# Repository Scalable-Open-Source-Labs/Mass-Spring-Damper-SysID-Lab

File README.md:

# Mass Spring Damper SysID Lab

A low-cost dynamics lab that allows students to perform System Identification on a real Mass-Spring-Damper system.

This is the source repo where you can download files for manufacturing: hardware, firmware, and enclosure design files. If you're looking for usage instructions or lab notes, head to the [user guide](https://monasheng.gitbook.io/scalable-labs/mass-spring-damper-sysid).

*Designed by Michael Ruppe for Monash University in partnership with MathWorks®*

## Repo map

| Path | What it is |
|---|---|
| [`PCB/`](PCB/README.md) | KiCad hardware source for the main board and carriage |
| [`Enclosure/`](Enclosure/README.md) | 3D-printable case, guide rail, and lasercut acrylic lid |
| [`firmware-mass-spring-damper-sys-id-lab/`](firmware-mass-spring-damper-sys-id-lab/README.md) | Arduino sketch for the RP2040 main board |
| [`Images/`](Images/) | Photos used in the assembly guide |
| [`Assembly-Instructions.md`](Assembly-Instructions.md) | Step-by-step mechanical build guide |
| [`Programming-Instructions.md`](Programming-Instructions.md) | Flashing and firmware dev setup |
| [`Ordering-Instructions.md`](Ordering-Instructions.md) | Bill of materials and where to order/fabricate each part |
| [`JLCPCB-Ordering-Instructions.md`](JLCPCB-Ordering-Instructions.md) | Step-by-step JLCPCB order for the fabricated and assembled boards |
| [`RELEASING.md`](RELEASING.md) | Maintainer checklist for cutting a tagged release |

## Getting started

- [Ordering Instructions](Ordering-Instructions.md)
  - [JLCPCB Ordering Instructions](JLCPCB-Ordering-Instructions.md)
- [Assembly Instructions](Assembly-Instructions.md)
- [Programming Instructions](Programming-Instructions.md)
- [Latest Project Release](https://github.com/Scaleable-Open-Source-Labs/Mass-Spring-Damper-SysID-Lab/releases/latest) - A downloadable bundle of all project files to complete this project: 3D Printing, PCBA, Lasercutting

## License

This project is licensed under the [MIT License](LICENSE).

Bundled third-party content — KiCad symbol/footprint libraries and vendor 3D step models under `PCB/main-board/packages3D/` and `PCB/carriage/CAD/`, and the patched `LedControl` fork used by the firmware (see [firmware README](firmware-mass-spring-damper-sys-id-lab/README.md)) — retains its original license terms.

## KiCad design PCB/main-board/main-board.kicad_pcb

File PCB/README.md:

# PCB

## KiCad Projects

| Project | Purpose |
|---|---|
| [`main-board/`](main-board/) | RP2040 controller board. Reads the linear encoder, drives the 7-segment display, exposes captured motion data over USB as a virtual FAT12 drive |
| [`carriage/`](carriage/) | The moving carriage PCB that rides the guide rail, carrying the linear encoder strip |

## Datasheets

[`Datasheet/`](Datasheet/) Each schematic symbol's `Datasheet` field links to it with a path relative to its own project folder (e.g. `../Datasheet/SMTSO.pdf`), so this directory should only ever contain files that a `.kicad_sch` actually references. Call up a datasheet from within the schematic editor by hovering over a symbol and pressing the 'D' key.

Datasheets for parts that aren't placed as KiCad components (hand-assembly hardware sourced in [Ordering-Instructions.md](../Ordering-Instructions.md), like the carriage-capture bolt) belong in the root [`Datasheets/`](../Datasheets/) directory instead, not here.

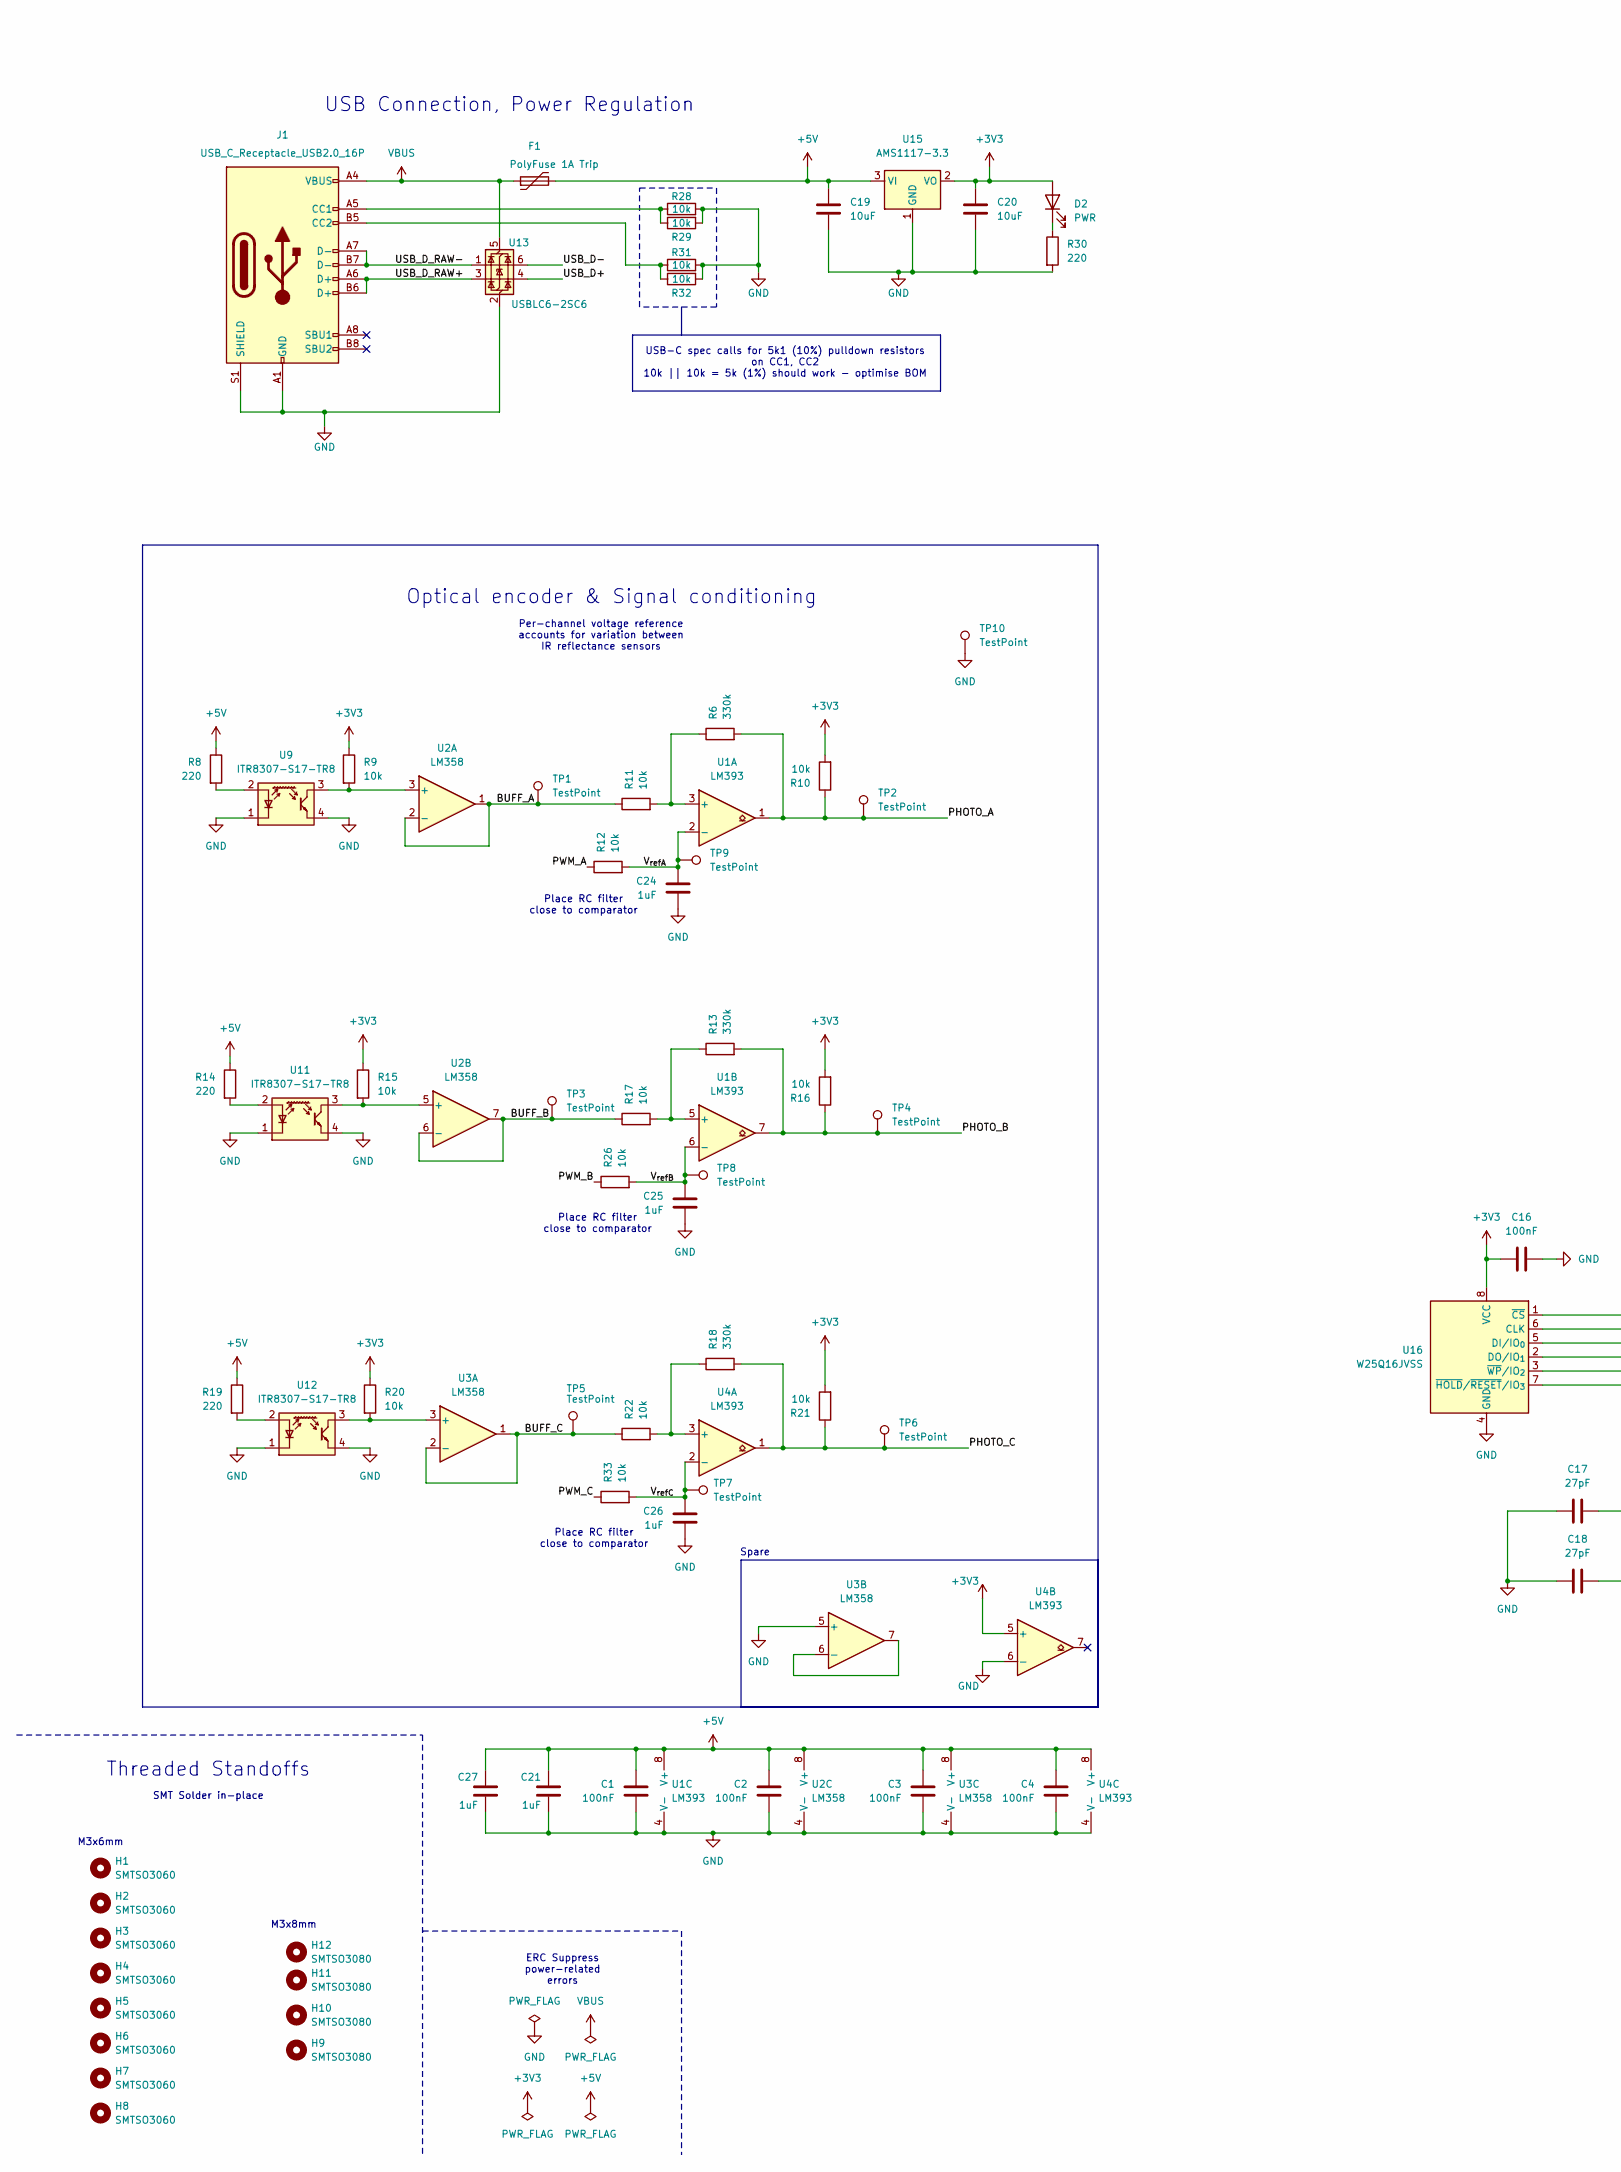
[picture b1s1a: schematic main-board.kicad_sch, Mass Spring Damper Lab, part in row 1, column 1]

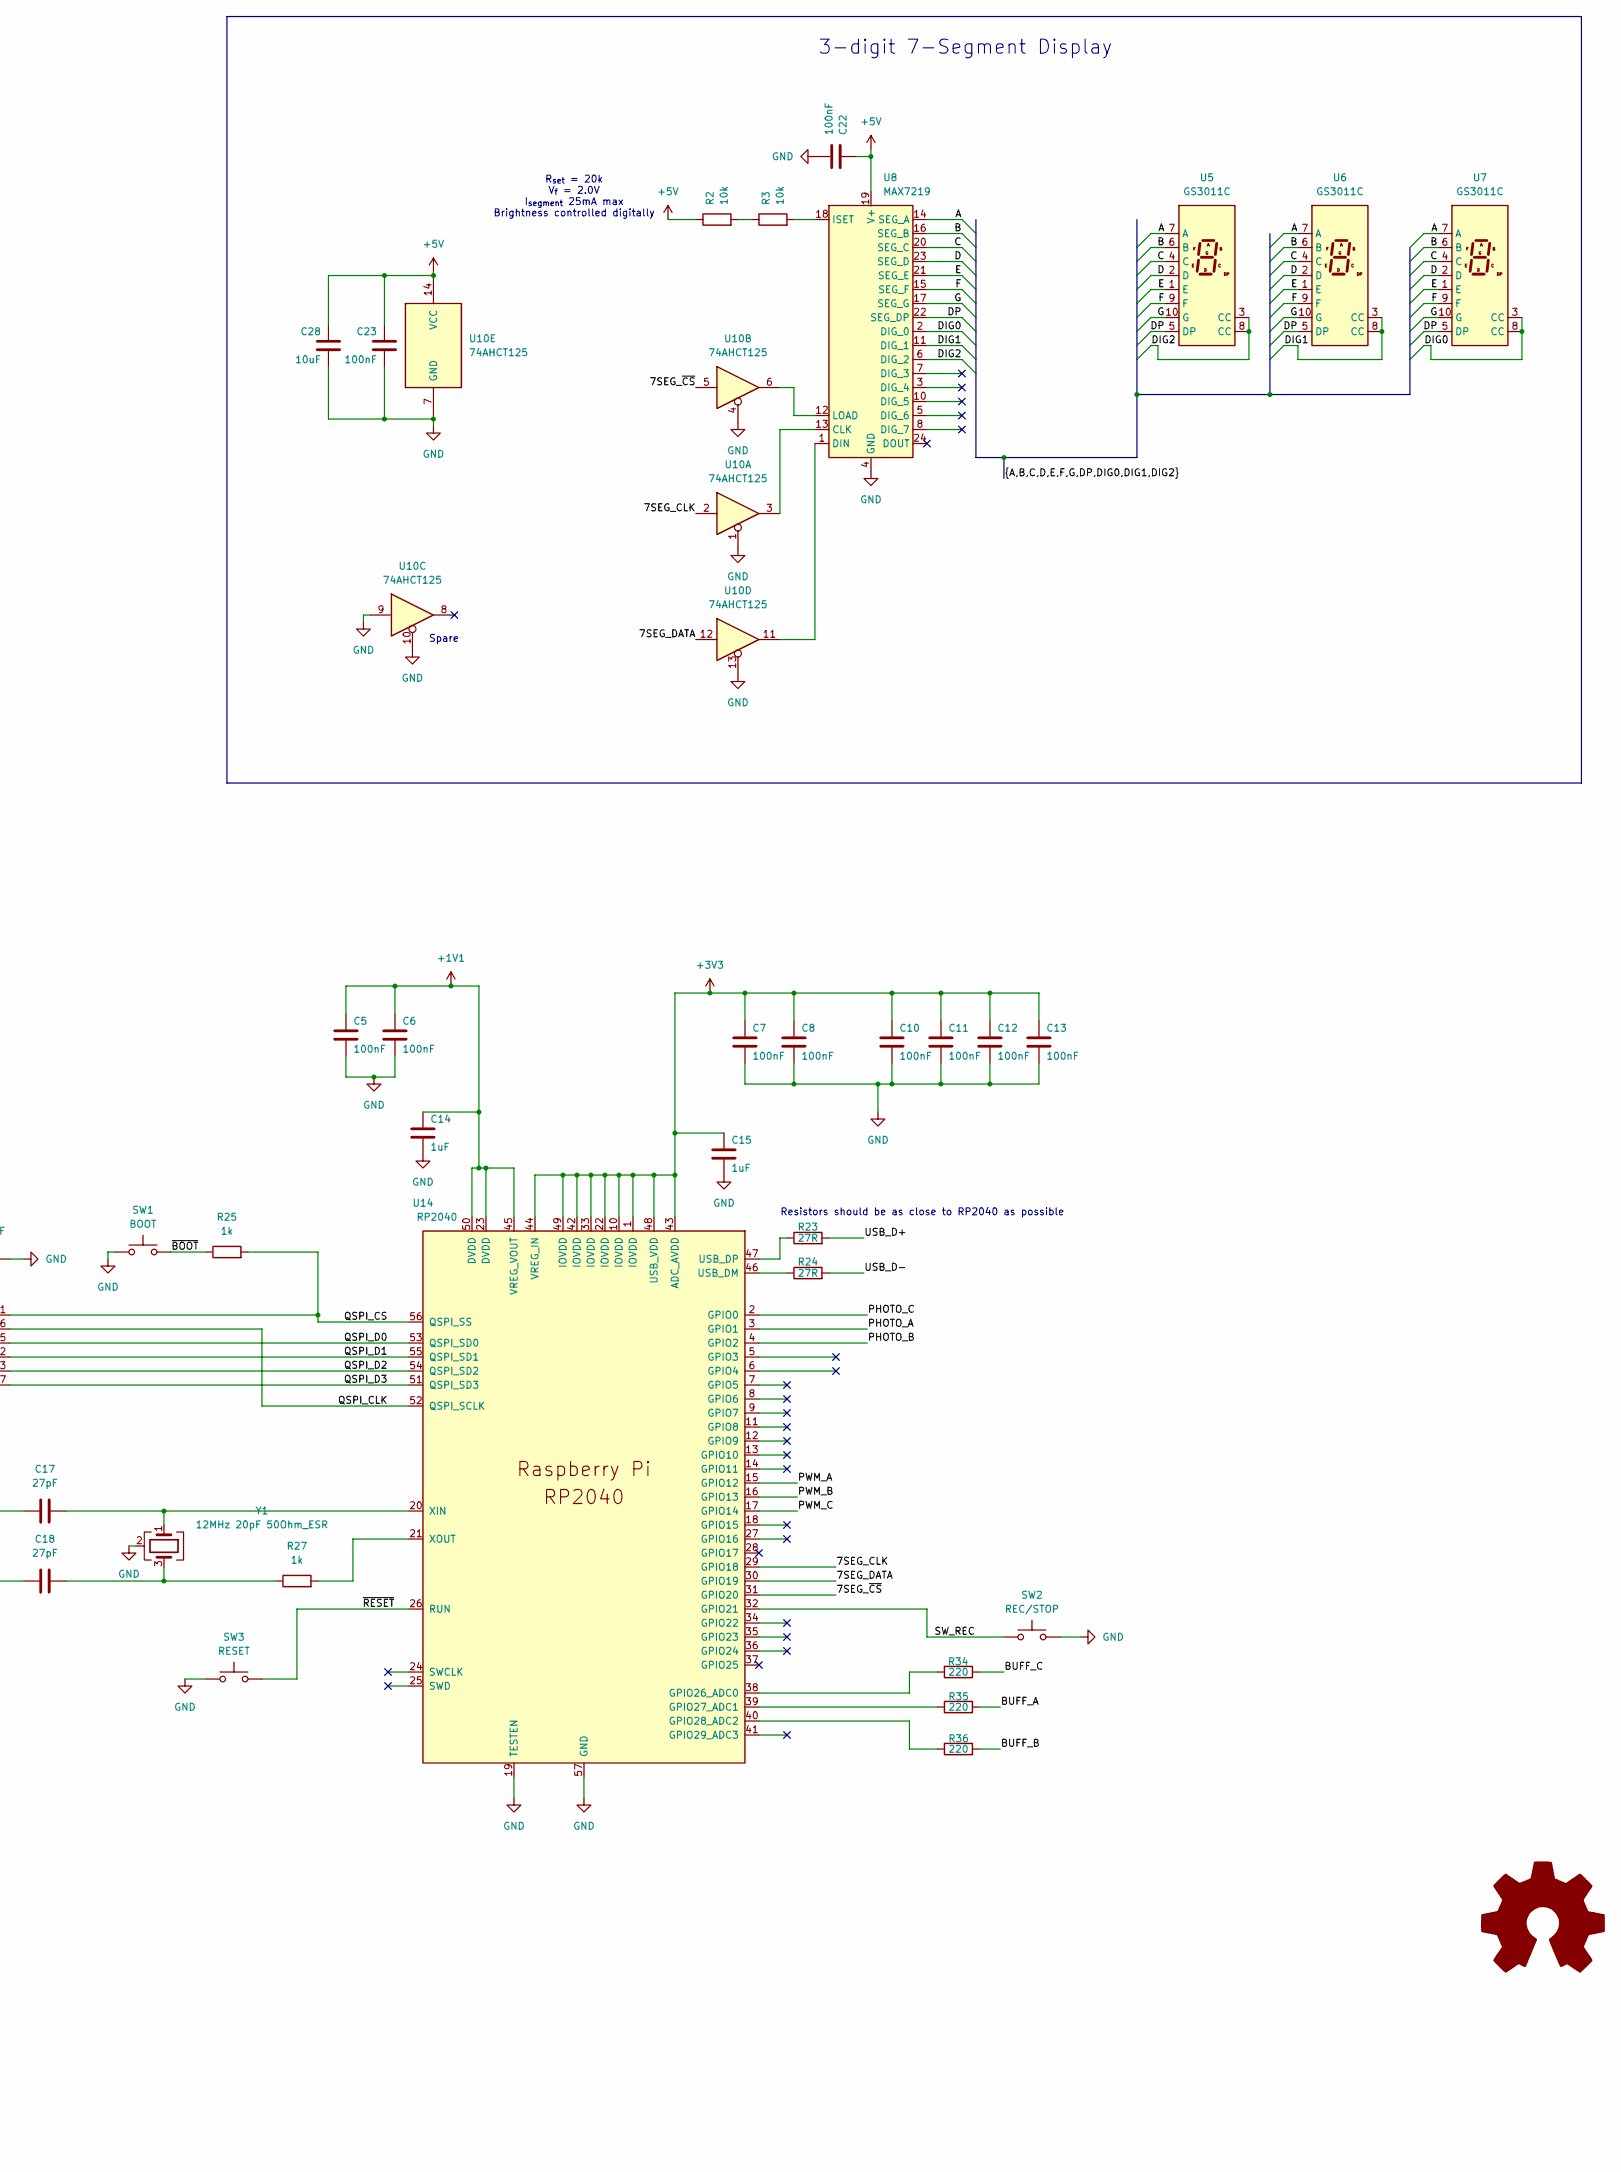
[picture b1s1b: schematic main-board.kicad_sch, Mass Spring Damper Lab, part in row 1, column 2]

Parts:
C1, C2, C3, C4, C5, C6, C7, C8, C10, C11, C12, C13, C16, C22, C23: 100nF; C_0603_1608Metric; LCSC Part # C14663
C14, C15, C21, C24, C25, C26, C27: 1uF; C_0603_1608Metric; LCSC Part # C15849
C17, C18: 27pF; C_0603_1608Metric; LCSC Part # C1656
C19, C20, C28: 10uF; C_0603_1608Metric; LCSC Part # C19702
D2: PWR; LED_0603_1608Metric; LCSC Part # C965807
F1: PolyFuse 1A Trip; R_1206_3216Metric; LCSC Part # C720075
H1, H2, H3, H4, H5, H6, H7, H8: SMTSO3060; MountingHole_SMTSO3060_3.2mm_M3; LCSC Part # C2915637
H9, H10, H11, H12: SMTSO3080; MountingHole_SMTSO3080_3.2mm_M3; LCSC Part # C2916369
J1: USB_C_Receptacle_USB2.0_16P; USB_C_Receptacle_HCTL_HC-TYPE-C-16P-01A; LCSC Part # C2894897
R2, R3, R9, R10, R11, R12, R15, R16, R17, R20, R21, R22, R26, R28, R29, R31, R32, R33: 10k; R_0603_1608Metric; LCSC Part # C25804
R6, R13, R18: 330k; R_0603_1608Metric; LCSC Part # C23137
R8, R14, R19, R30, R34, R35, R36: 220; R_0603_1608Metric; LCSC Part # C22962
R23, R24: 27R; R_0603_1608Metric; LCSC Part # C25190
R25, R27: 1k; R_0603_1608Metric; LCSC Part # C21190
SW1: BOOT; SW_Push_1P1T_NO_E-Switch_TL3301NxxxxxG; LCSC Part # C455109
SW2: REC/STOP; SW_SPST_Omron_B3F-40xx; LCSC Part # C84931
SW3: RESET; SW_SPST_Omron_B3F-40xx; LCSC Part # C84931
TP1, TP2, TP3, TP4, TP5, TP6, TP7, TP8, TP9, TP10: TestPoint; TestPoint_Pad_D1.5mm
U1, U4: LM393; SOIC-8_3.9x4.9mm_P1.27mm; LCSC Part # C32901
U2, U3: LM358; SOIC-8_3.9x4.9mm_P1.27mm; LCSC Part # C9418
U5, U6, U7: GS3011C; GS3011; LCSC Part # C22462660
U8: MAX7219; SOIC-24W_7.5x15.4mm_P1.27mm; LCSC Part # C49443603
U9, U11, U12: ITR8307-S17-TR8; Everlight_ITR1201SR10AR; LCSC Part # C81632
U10: 74AHCT125; SOIC-14_3.9x8.7mm_P1.27mm; LCSC Part # C5962
U13: USBLC6-2SC6; SOT-23-6; LCSC Part # C2687116
U14: RP2040; RP2040-QFN-56; PARTREV 1.6.1; LCSC Part # C2040
U15: AMS1117-3.3; SOT-223-3_TabPin2; LCSC Part # C6186
U16: W25Q16JVSS; SOIC-8_5.3x5.3mm_P1.27mm; LCSC Part # C82317
Y1: 12MHz 20pF 50Ohm_ESR; Crystal_SMD_3225-4Pin_3.2x2.5mm; LCSC Part # C133334

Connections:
+1V1: C5.1, C6.1, C14.1, U14.23 (DVDD), U14.45 (VREG_VOUT), U14.50 (DVDD)
+3V3: C7.1, C8.1, C10.1, C11.1, C12.1, C13.1, C15.1, C16.1, C20.1, D2.2 (A), R9.1, R10.2, R15.1, R16.2, R20.1, R21.2, U4.5 (+), U14.1 (IOVDD), U14.10 (IOVDD), U14.22 (IOVDD), U14.33 (IOVDD), U14.42 (IOVDD), U14.43 (ADC_AVDD), U14.44 (VREG_IN), U14.48 (USB_VDD), U14.49 (IOVDD), U15.2 (VO), U16.8 (VCC)
+5V: C1.1, C2.1, C3.1, C4.1, C19.1, C21.1, C22.1, C23.1, C27.1, C28.1, F1.2, R2.1, R8.1, R14.1, R19.1, U1.8 (V+), U2.8 (V+), U3.8 (V+), U4.8 (V+), U8.19 (V+), U10.14 (VCC), U15.3 (VI)
/7SEG_CLK: U10.2, U14.29 (GPIO18)
/7SEG_DATA: U10.12, U14.30 (GPIO19)
/7SEG_~CS: U10.5, U14.31 (GPIO20)
/A: U5.7 (A), U6.7 (A), U7.7 (A), U8.14 (SEG_A)
/B: U5.6 (B), U6.6 (B), U7.6 (B), U8.16 (SEG_B)
/BUFF_A: R11.1, R35.2, TP1.1 (1_1), U2.1, U2.2 (-)
/BUFF_B: R17.1, R36.2, TP3.1 (1_1), U2.6 (-), U2.7
/BUFF_C: R22.1, R34.1, TP5.1 (1_1), U3.1, U3.2 (-)
/C: U5.4 (C), U6.4 (C), U7.4 (C), U8.20 (SEG_C)
/D: U5.2 (D), U6.2 (D), U7.2 (D), U8.23 (SEG_D)
/DIG0: U7.3 (CC), U7.8 (CC), U8.2 (DIG_0)
/DIG1: U6.3 (CC), U6.8 (CC), U8.11 (DIG_1)
/DIG2: U5.3 (CC), U5.8 (CC), U8.6 (DIG_2)
/DP: U5.5 (DP), U6.5 (DP), U7.5 (DP), U8.22 (SEG_DP)
/E: U5.1 (E), U6.1 (E), U7.1 (E), U8.21 (SEG_E)
/F: U5.9 (F), U6.9 (F), U7.9 (F), U8.15 (SEG_F)
/G: U5.10 (G), U6.10 (G), U7.10 (G), U8.17 (SEG_G)
/PHOTO_A: R6.2, R10.1, TP2.1 (1_1), U1.1, U14.3 (GPIO1)
/PHOTO_B: R13.2, R16.1, TP4.1 (1_1), U1.7, U14.4 (GPIO2)
/PHOTO_C: R18.2, R21.1, TP6.1 (1_1), U4.1, U14.2 (GPIO0)
/PWM_A: R12.1, U14.15 (GPIO12)
/PWM_B: R26.1, U14.16 (GPIO13)
/PWM_C: R33.1, U14.17 (GPIO14)
/QSPI_CLK: U14.52 (QSPI_SCLK), U16.6 (CLK)
/QSPI_CS: R25.2, U14.56 (QSPI_SS), U16.1 (~CS)
/QSPI_D0: U14.53 (QSPI_SD0), U16.5 (DI/IO_{0})
/QSPI_D1: U14.55 (QSPI_SD1), U16.2 (DO/IO_{1})
/QSPI_D2: U14.54 (QSPI_SD2), U16.3 (~WP/IO_{2})
/QSPI_D3: U14.51 (QSPI_SD3), U16.7 (~HOLD/~RESET/IO_{3})
/SW_REC: SW2.1, U14.32 (GPIO21)
/USB_D+: R23.2, U13.4 (I/O2)
/USB_D-: R24.2, U13.6 (I/O1)
/USB_D_RAW+: J1.A6 (D+), J1.B6 (D+), U13.3 (I/O2)
/USB_D_RAW-: J1.A7 (D-), J1.B7 (D-), U13.1 (I/O1)
/V_{refA}: C24.1, R12.2, TP9.1 (1_1), U1.2 (-)
/V_{refB}: C25.1, R26.2, TP8.1 (1_1), U1.6 (-)
/V_{refC}: C26.1, R33.2, TP7.1 (1_1), U4.2 (-)
/~BOOT: R25.1, SW1.1
/~RESET: SW3.1, U14.26 (RUN)
GND: C1.2, C2.2, C3.2, C4.2, C5.2, C6.2, C7.2, C8.2, C10.2, C11.2, C12.2, C13.2, C14.2, C15.2, C16.2, C17.1, C18.1, C19.2, C20.2, C21.2, C22.2, C23.2, C24.2, C25.2, C26.2, C27.2, C28.2, J1.A1 (GND), J1.A12 (GND), J1.B1 (GND), J1.B12 (GND), J1.S1 (SHIELD), R28.2, R29.2, R30.2, R31.2, R32.2, SW1.2, SW2.2, SW3.2, TP10.1 (1_1), U1.4 (V-), U2.4 (V-), U3.4 (V-), U3.5 (+), U4.4 (V-), U4.6 (-), U8.4 (GND), U8.9 (GND), U9.1 (K), U9.4, U10.1, U10.4, U10.7 (GND), U10.9, U10.10, U10.13, U11.1 (K), U11.4, U12.1 (K), U12.4, U13.2 (GND), U14.19 (TESTEN), U14.57 (GND), U15.1 (GND), U16.4 (GND), Y1.2 (G), Y1.4 (G)
unnamed: C18.2, R27.1, Y1.3
unnamed: D2.1 (K), R30.1
unnamed: J1.A5 (CC1), R28.1, R29.1
unnamed: J1.B5 (CC2), R31.1, R32.1
unnamed: R2.2, R3.1
unnamed: R6.1, R11.2, U1.3 (+)
unnamed: R13.1, R17.2, U1.5 (+)
unnamed: R9.2, U2.3 (+), U9.3
unnamed: R15.2, U2.5 (+), U11.3
unnamed: R20.2, U3.3 (+), U12.3
unnamed: U3.6 (-), U3.7
unnamed: R18.1, R22.2, U4.3 (+)
unnamed: U8.13 (CLK), U10.3
unnamed: U8.1 (DIN), U10.11
unnamed: R3.2, U8.18 (ISET)
unnamed: U8.12 (LOAD), U10.6
unnamed: R8.2, U9.2 (A)
unnamed: R14.2, U11.2 (A)
unnamed: R19.2, U12.2 (A)
unnamed: R34.2, U14.38 (GPIO26_ADC0)
unnamed: R35.1, U14.39 (GPIO27_ADC1)
unnamed: R36.1, U14.40 (GPIO28_ADC2)
unnamed: R24.1, U14.46 (USB_DM)
unnamed: R23.1, U14.47 (USB_DP)
unnamed: C17.2, U14.20 (XIN), Y1.1
unnamed: R27.2, U14.21 (XOUT)
VBUS: F1.1, J1.A4 (VBUS), J1.A9 (VBUS), J1.B4 (VBUS), J1.B9 (VBUS), U13.5 (VBUS)

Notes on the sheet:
USB-C spec calls for 5k1 (10%) pulldown resistors on CC1, CC2 10k || 10k = 5k (1%) should work - optimise BOM
Spare
M3x6mm
Place RC filter close to comparator
Resistors should be as close to RP2040 as possible
Per-channel voltage reference accounts for variation between IR reflectance sensors
3-digit 7-Segment Display
Threaded Standoffs
USB Connection, Power Regulation
ERC Suppress power-related errors
SMT Solder in-place
R_{set} = 20k V_{f} = 2.0V I_{segment} 25mA max Brightness controlled digitally
Optical encoder & Signal conditioning
M3x8mm

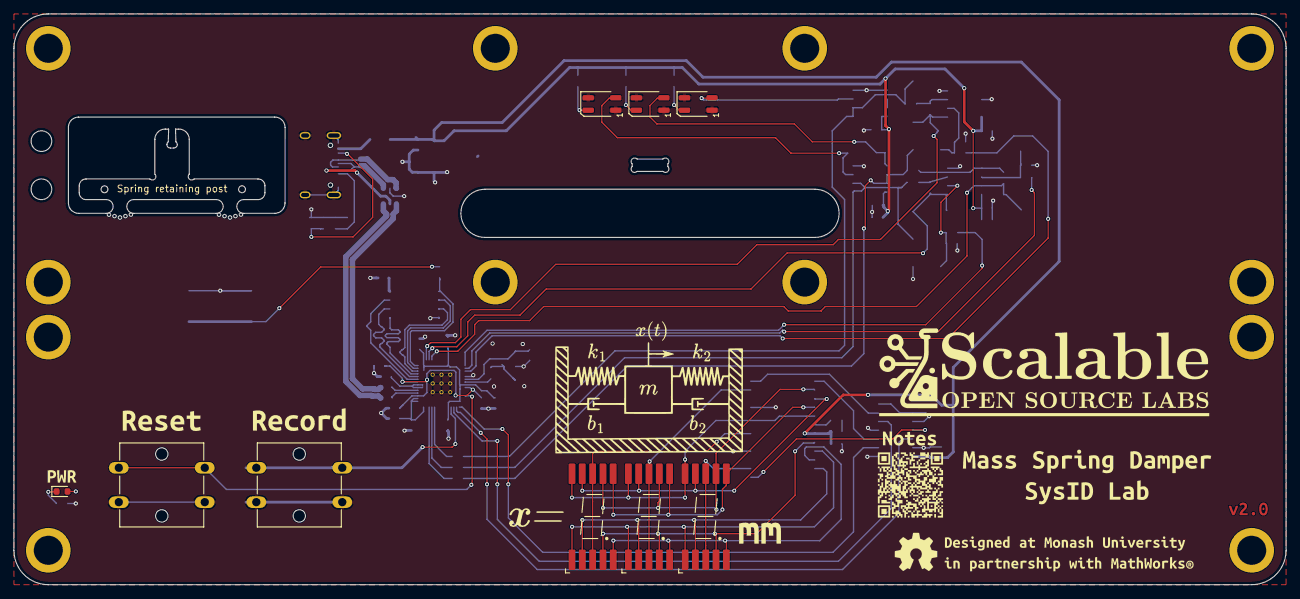
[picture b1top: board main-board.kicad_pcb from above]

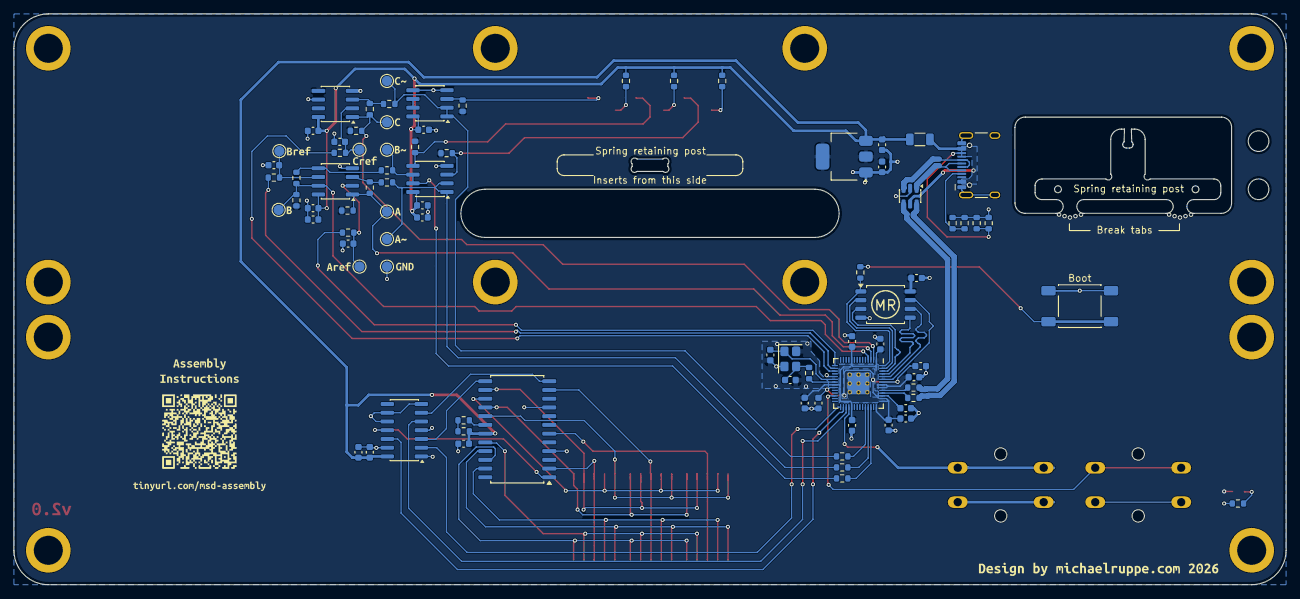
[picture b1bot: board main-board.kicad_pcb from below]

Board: 2 copper layers, 185.0 x 83.0 mm, 130 parts (105 on the bottom side), 70 nets.

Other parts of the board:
kibuzzard-6A5D9E3D: G***; kibuzzard-6A5D9E3D
kibuzzard-6A5DA214: G***; kibuzzard-6A5DA214
kibuzzard-6A5DFDED: G***; kibuzzard-6A5DFDED
kibuzzard-6A5DFE62: G***; kibuzzard-6A5DFE62
kibuzzard-6A9CABE9: G***; kibuzzard-6A9CABE9
kibuzzard-6A9CB9E8: G***; kibuzzard-6A9CB9E8
kibuzzard-6A9CBA3E: G***; kibuzzard-6A9CBA3E
kibuzzard-6A9CBA9F: G***; kibuzzard-6A9CBA9F
kibuzzard-6A9CBA16: G***; kibuzzard-6A9CBA16
kibuzzard-6A9CBA29: G***; kibuzzard-6A9CBA29
kibuzzard-6A9CBA31: G***; kibuzzard-6A9CBA31
kibuzzard-6A9CBA47: G***; kibuzzard-6A9CBA47
kibuzzard-6A9CBA92: G***; kibuzzard-6A9CBA92
kibuzzard-6A9CBA99: G***; kibuzzard-6A9CBA99
kibuzzard-6A9CBB45: G***; kibuzzard-6A9CBB45
kibuzzard-6A601CB9: G***; kibuzzard-6A601CB9
kibuzzard-6A601CBF: G***; kibuzzard-6A601CBF
kibuzzard-6A601CD4: G***; kibuzzard-6A601CD4
kibuzzard-6A815F94: G***; kibuzzard-6A815F94
kibuzzard-6930AF86: G***; kibuzzard-6930AF86
kibuzzard-69645CED: G***; kibuzzard-69645CED
kibuzzard-6978363D: G***; kibuzzard-6978363D
kibuzzard-69310180: G***; kibuzzard-69310180
kibuzzard-69783696: G***; kibuzzard-69783696
mousebite1, mousebite2: VAL**; mouse-bite-2mm-4mm-single-sided

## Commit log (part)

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2026-02-17 add instructions and images
2026-02-17 typo
2026-02-17 update instructions
2026-02-17 add image
2026-02-17 add final assembly image
2026-06-29 Add pliers to tool list
2026-06-29 refer to screws as 'long' and 'short' for human readableness
2026-06-29 enhance readability
2026-06-29 releases link: use latest release

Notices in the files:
README.md:
License: MIT
